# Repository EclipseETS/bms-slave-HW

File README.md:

# bms-slave-HW
Kicad project for slave board of the Eclipse solar car BMS

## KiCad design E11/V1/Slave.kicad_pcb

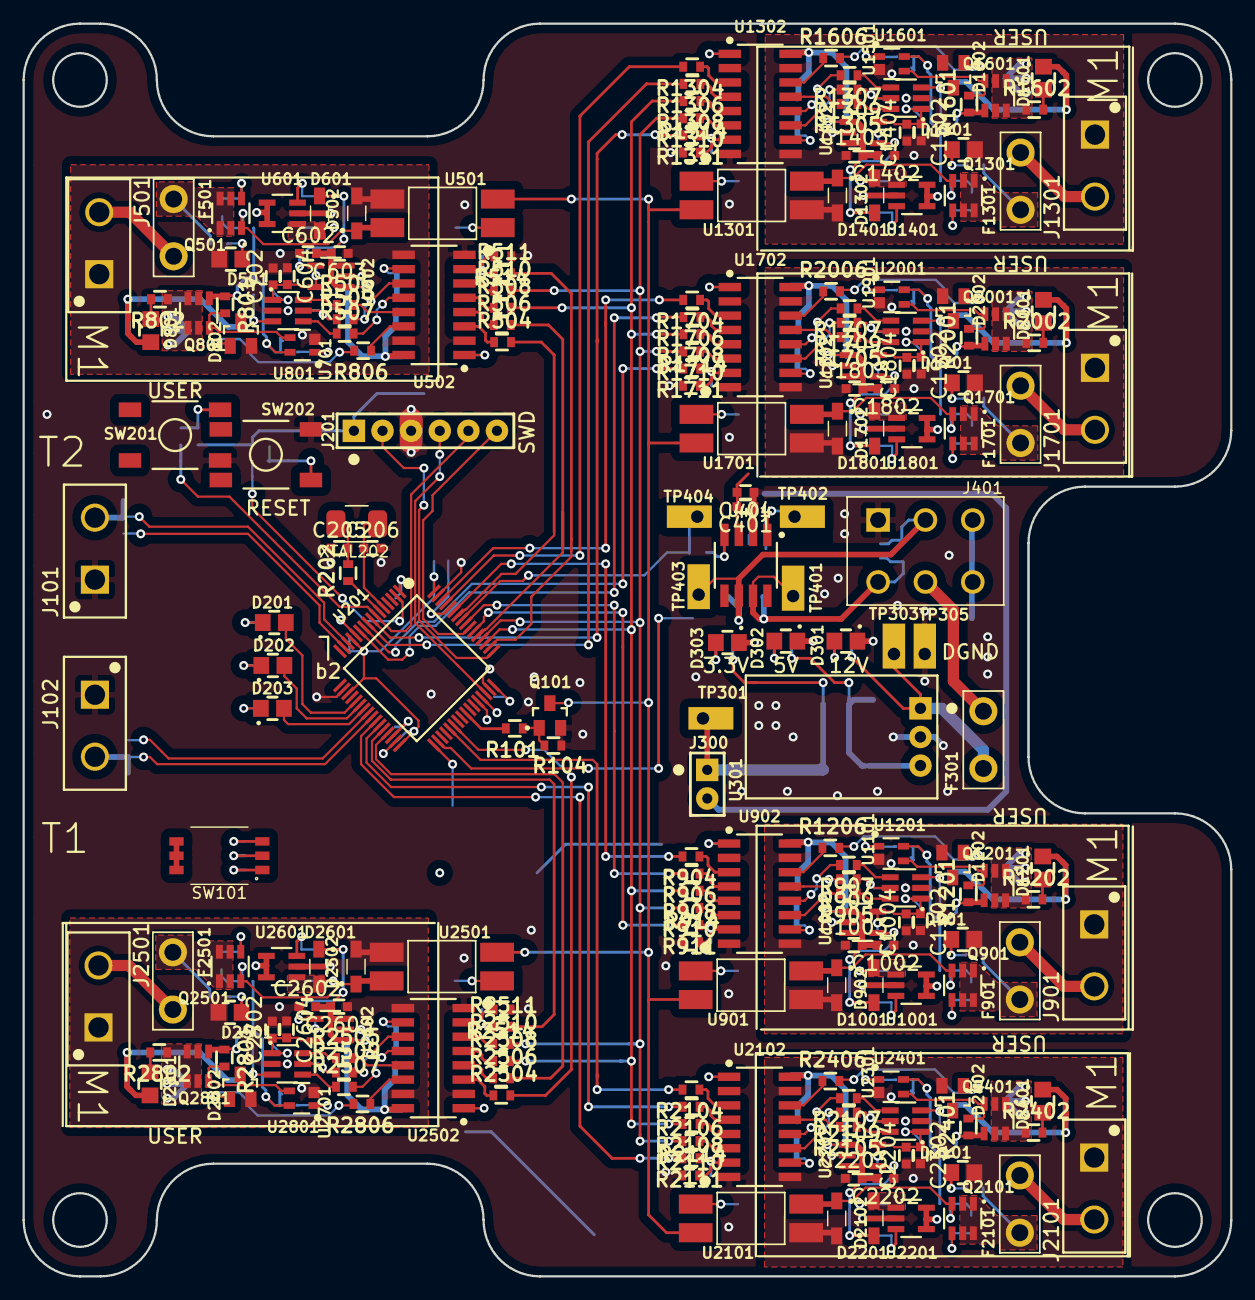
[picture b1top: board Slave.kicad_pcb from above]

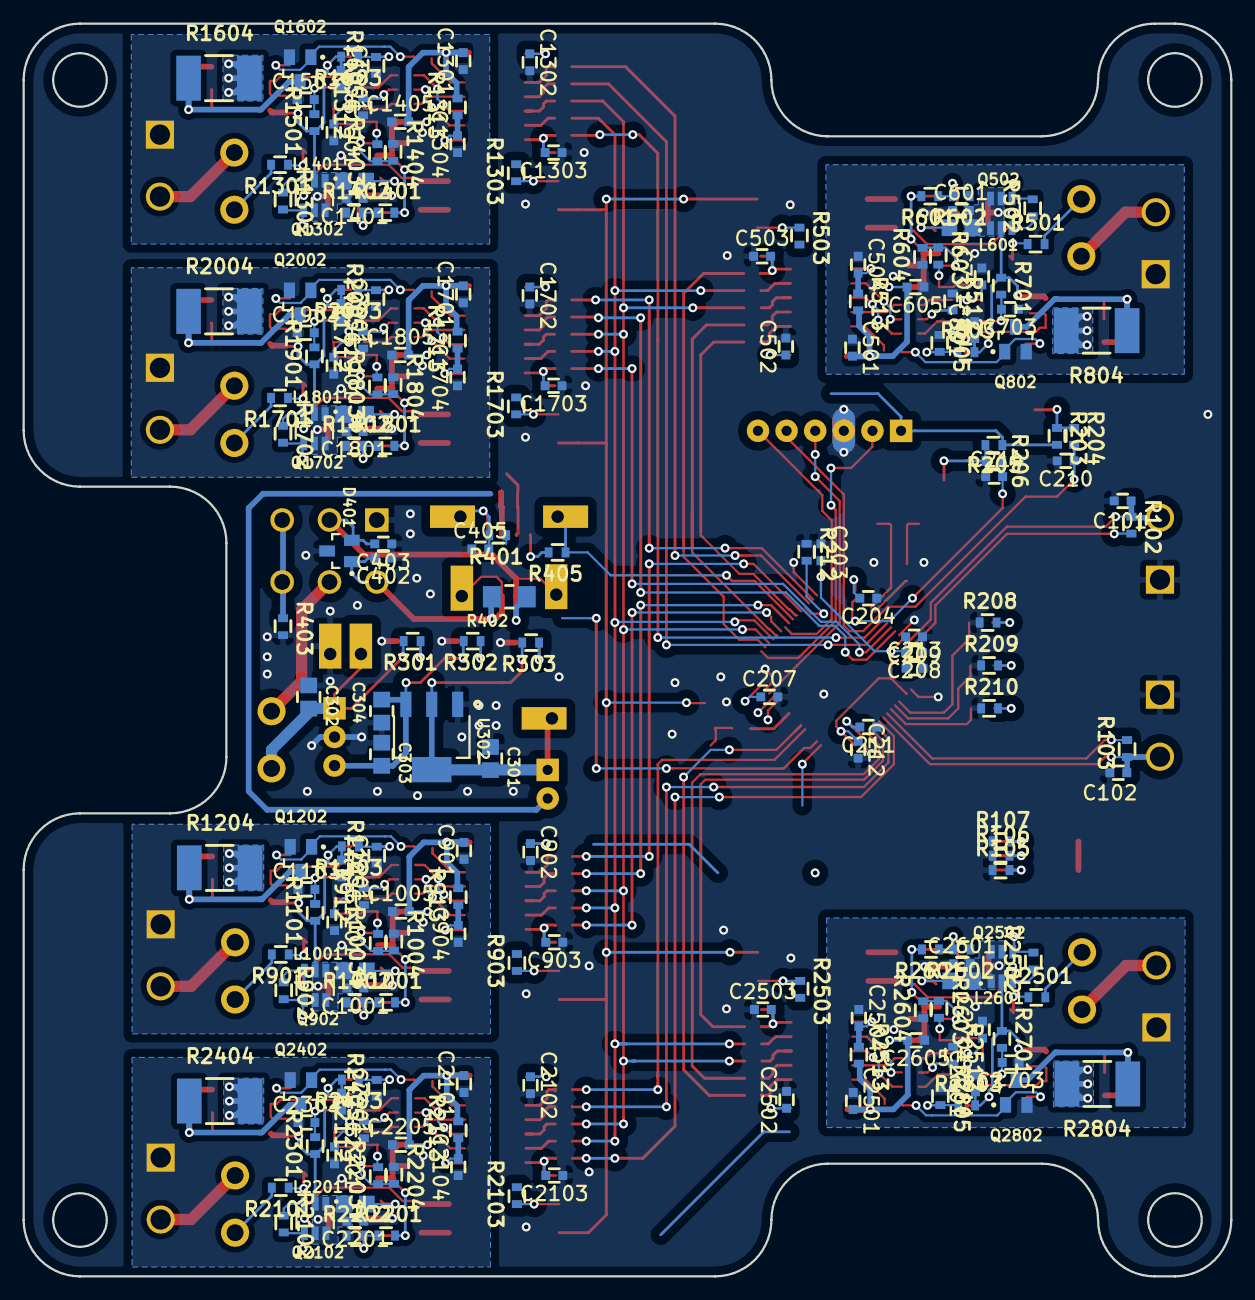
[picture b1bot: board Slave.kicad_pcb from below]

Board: 2 copper layers, 107.2 x 111.2 mm, 411 parts (191 on the bottom side), 263 nets.

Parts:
C101, C102, C204, C208, C401: 885012107015; C0603
C203, C207, C210, C212, C213, C214, C404: 885012207098; C0603
C205, C206, C402, C403: 885012007053; C0603
C209: 885012207092; C0603
C211: 885012107018; C0603
C301: 885012107005; C0805
C302, C303: 885012107018; C0805
C304: 885012107014; C0805
C405: 885012207080; C0603
C501, C502, C504, C702, C801, C901, C902, C904, C1102, C1201, C1301, C1302, C1304, C1502, C1601, C1701, C1702, C1704, C1902, C2001, C2101, C2102, C2104, C2302, C2401, C2501, C2502, C2504, C2702, C2801: 885012206095; C0603
C503, C903, C1303, C1703, C2103, C2503: 885012206077; C0603
C601, C602, C603, C604, C605, C1001, C1002, C1003, C1004, C1005, C1401, C1402, C1403, C1404, C1405, C1801, C1802, C1803, C1804, C1805, C2201, C2202, C2203, C2204, C2205, C2601, C2602, C2603, C2604, C2605: GRM188R61C106KAALD; C0603
C701, C1101, C1501, C1901, C2301, C2701: 885012106022; C0603
C703, C1103, C1503, C1903, C2303, C2703: 885012206073; C0603
D201, D301, D302, D303, D801, D1201, D1601, D2001, D2401, D2801: 150080VS75000; LED_0805_GREEN
D202: 150080YS75000; LED_0805_YELLOW
D203, D501, D901, D1301, D1701, D2101, D2501: 150080RS75000; LED_0805_RED
D401: D1213A-02SOL-7; SOT-23-3
D502, D601, D902, D1001, D1302, D1401, D1702, D1801, D2102, D2201, D2502, D2601: NSR0530HT1G; SOD-323
D802, D1202, D1602, D2002, D2402, D2802: MMBZ12VALT1G; SOT-23-3
F301, F501, F901, F1301, F1701, F2101, F2501: 39511000440; TE5_395
J101, J102, J501, J901, J1301, J1701, J2101, J2501: 64900221122
J201: Header_Male_Pin_2.54mm_1X6_,_Unshrouded; Headers_2.54mm_1X6
J300: Header_Male_Pin_2.54mm_1X2_,_Unshrouded; Headers_2.54mm_1X2
J401: 64900621122
L601, L1001, L1401, L1801, L2201, L2601: MLZ2012N101LT000; I0805
Q101: 2N7002P,215; SOT-23-3
Q501, Q502, Q801, Q901, Q902, Q1201, Q1301, Q1302, Q1601, Q1701, Q1702, Q2001, Q2101, Q2102, Q2401, Q2501, Q2502, Q2801: CPH6347-TL-W; TSOT-23-6
Q802, Q1202, Q1602, Q2002, Q2402, Q2802: BSS806NH6327XTSA1; SOT-23-3
R101, R208, R209, R210, R303: RC0805JR-07470RL; R0603
R102, R103: RC0805JR-0733KL; R0603
R104, R203, R205, R301: RC0805JR-074K7L; R0603
R105, R106, R107: RC0603JR-07470RL; R0603
R202, R403: RC0805JR-070RL; R0603
R204, R206, R401, R405: RC0805JR-07100RL; R0603
R212: RC0805JR-0710KL; R0603
R302: RC0805JR-071KL; R0603
R402: RC1206JR-07120RL; R1206
R501, R802, R901, R1202, R1301, R1602, R1701, R2002, R2101, R2402, R2501, R2802: RC0603JR-071KL; R0603
R502, R514, R801, R902, R914, R1201, R1302, R1314, R1601, R1702, R1714, R2001, R2102, R2114, R2401, R2502, R2514, R2801: RC0603JR-07470KL; R0603
R503, R903, R1303, R1703, R2103, R2503: RC0603JR-07330RL; R0603
R504, R505, R506, R507, R508, R509, R701, R904, R905, R906, R907, R908, R909, R1101, R1304, R1305, R1306, R1307, R1308, R1309, R1501, R1704, R1705, R1706, R1707, R1708, R1709, R1901, R2104, R2105, R2106, R2107, R2108, R2109, R2301, R2504, R2505, R2506, R2507, R2508, R2509, R2701: RC0603FR-07100RL; R0603
R510, R511, R512, R513, R603, R910, R911, R912, R913, R1003, R1310, R1311, R1312, R1313, R1403, R1710, R1711, R1712, R1713, R1803, R2110, R2111, R2112, R2113, R2203, R2510, R2511, R2512, R2513, R2603: RC0603JR-074K7L; R0603
R601, R1001, R1401, R1801, R2201, R2601: RC0603JR-071ML; R0603
R602, R1002, R1402, R1802, R2202, R2602: RC0603FR-07324KL; R0603
R604, R1004, R1404, R1804, R2204, R2604: RC0603FR-0712K1L; R0603
R803, R1203, R1603, R2003, R2403, R2803: RC0603JR-07560KL; R0603
R804, R1204, R1604, R2004, R2404, R2804: 352210RJT; R2512
R805, R1205, R1605, R2005, R2405, R2805: RC0603JR-07100KL; R0603
R806, R1206, R1606, R2006, R2406, R2806: RC0603JR-076K8L; R0603
SW101: DIP_SW_3; 416131160803
SW201, SW202: PTS645SM43SMTR92; PTS645_6X6X4_SMD
TP301, TP303, TP305, TP401, TP402, TP403, TP404: Test_Point_THM; Keystone_5001
U201: STM32F446RE; LQFP-64
U301: OKI-78SR-5/1.5-W36-C; OKI-78SR_Horizontal
U302: AZ1117IH-3.3TRG1; SOT-223-3
U401: SN65HVD232DR; SOIC-8
U501, U901, U1301, U1701, U2101, U2501: LTV-816S; 4-SMD
U502, U902, U1302, U1702, U2102, U2502: SI8641AB-B-IS1; SOIC-16
U601, U1001, U1401, U1801, U2201, U2601: AP3015KTR-G1; SOT-23-5
U602, U1002, U1402, U1802, U2202, U2602: AP2202K-ADJTRG1; SOT-23-5
U701, U1101, U1501, U1901, U2301, U2701: ADC121S021CIMF/NOPB; SOT-23-6
U801, U1201, U1601, U2001, U2401, U2801: ADCMP350YKSZ-REEL7; SC70-4
XTAL202: 7A-8.000MAHJ-T; TXC_7A_Series

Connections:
3.3V: C301.2, J300.1, R303.2, TP301.1, U302.2, U302.4
5V: C303.2, C304.2, R302.2, U301.3, U302.3
12V: C302.2, F301.2, R301.2, TP303.1, U301.1
/BALANCING_PWM_1: R504.2, U201.58
/BALANCING_PWM_2: R904.2, U201.59
/BALANCING_PWM_3: R1304.2, U201.61
/BALANCING_PWM_4: R1704.2, U201.62
/BALANCING_PWM_5: R2104.2, U201.37
/BALANCING_PWM_6: R2504.2, U201.38
/CAN1/CAN_N: C403.2, D401.2, J401.2, R402.2, TP403.1, U401.6
/CAN1/CAN_P: C402.2, D401.1, J401.4, R402.1, TP401.1, U401.7
/CAN1/Shield1: J401.3, J401.6, R403.1
/CAN2_RX: R405.1, TP404.1, U201.57
/CAN2_TX: R401.1, U201.34
/CS_1: R506.2, U201.53
/CS_2: R906.2, U201.56
/CS_3: R1306.2, U201.9
/CS_4: R1706.2, U201.11
/CS_5: R2106.2, U201.27
/CS_6: R2506.2, U201.29
/DATA_ENABLE_1: R511.2, U201.50
/DATA_ENABLE_2: R911.2, U201.54
/DATA_ENABLE_3: R1311.2, U201.8
/DATA_ENABLE_4: R1711.2, U201.10
/DATA_ENABLE_5: R2111.2, U201.26
/DATA_ENABLE_6: R2511.2, U201.28
/ID_0: R105.2, SW101.1, U201.33
/ID_1: R106.2, SW101.2, U201.44
/ID_2: R107.2, SW101.3, U201.45
/MISO: R510.2, R910.2, R1310.2, R1710.2, R2110.2, R2510.2, U201.52
/Module 1/+VREF: C604.2, C701.1, C702.1, R603.2, U602.5, U701.1
/Module 1/BALANCE_PWM: R806.1, U502.14
/Module 1/BVDD: C501.2, C602.2, C603.2, C605.2, D601.1, R513.2, R601.2, U502.16, U602.1, U602.3
/Module 1/Balancing/Drain_P_Mosfet: Q801.1, Q801.2, Q801.5, Q801.6, R802.1, R804.2
/Module 1/CELL+: F501.2, Q501.1, Q501.2, Q501.5, Q501.6, R501.2
/Module 1/CELL-: C501.1, C504.1, C601.1, C602.1, C603.1, C604.1, C605.1, C701.2, C702.2, C703.1, C801.2, D501.2, D502.2, D802.2, J501.1, Q802.2, R512.1, R602.1, R604.1, R805.1, U501.3, U502.9, U502.15, U601.2, U602.2, U701.2, U801.2
/Module 1/CELL_Voltage: C601.2, C801.1, L601.1, Q502.1, Q502.2, Q502.5, Q502.6, Q801.4, R701.1, R801.1, R803.2, U601.4, U601.5, U801.4
/Module 1/CS: R505.2, U502.13
/Module 1/Power Supply Front End/SW: D601.2, L601.2, U601.1
/Module 1/SCLK: R507.2, U502.12
/Module 1/SDATA: R509.2, U502.11
/Module 1/Voltage Reading/CS: R505.1, U701.6
/Module 1/Voltage Reading/SCLK: R507.1, U701.4
/Module 1/Voltage Reading/SDATA: R509.1, R512.2, U701.5
/Module 2/+VREF: C1004.2, C1101.1, C1102.1, R1003.2, U1002.5, U1101.1
/Module 2/BALANCE_PWM: R1206.1, U902.14
/Module 2/BVDD: C901.2, C1002.2, C1003.2, C1005.2, D1001.1, R913.2, R1001.2, U902.16, U1002.1, U1002.3
/Module 2/Balancing/Drain_P_Mosfet: Q1201.1, Q1201.2, Q1201.5, Q1201.6, R1202.1, R1204.2
/Module 2/CELL+: F901.2, Q901.1, Q901.2, Q901.5, Q901.6, R901.2
/Module 2/CELL-: C901.1, C904.1, C1001.1, C1002.1, C1003.1, C1004.1, C1005.1, C1101.2, C1102.2, C1103.1, C1201.2, D901.2, D902.2, D1202.2, J901.1, Q1202.2, R912.1, R1002.1, R1004.1, R1205.1, U901.3, U902.9, U902.15, U1001.2, U1002.2, U1101.2, U1201.2
/Module 2/CELL_Voltage: C1001.2, C1201.1, L1001.1, Q902.1, Q902.2, Q902.5, Q902.6, Q1201.4, R1101.1, R1201.1, R1203.2, U1001.4, U1001.5, U1201.4
/Module 2/CS: R905.2, U902.13
/Module 2/Power Supply Front End/SW: D1001.2, L1001.2, U1001.1
/Module 2/SCLK: R907.2, U902.12
/Module 2/SDATA: R909.2, U902.11
/Module 2/Voltage Reading/CS: R905.1, U1101.6
/Module 2/Voltage Reading/SCLK: R907.1, U1101.4
/Module 2/Voltage Reading/SDATA: R909.1, R912.2, U1101.5
/Module 3/+VREF: C1404.2, C1501.1, C1502.1, R1403.2, U1402.5, U1501.1
/Module 3/BALANCE_PWM: R1606.1, U1302.14
/Module 3/BVDD: C1301.2, C1402.2, C1403.2, C1405.2, D1401.1, R1313.2, R1401.2, U1302.16, U1402.1, U1402.3
/Module 3/Balancing/Drain_P_Mosfet: Q1601.1, Q1601.2, Q1601.5, Q1601.6, R1602.1, R1604.2
/Module 3/CELL+: F1301.2, Q1301.1, Q1301.2, Q1301.5, Q1301.6, R1301.2
/Module 3/CELL-: C1301.1, C1304.1, C1401.1, C1402.1, C1403.1, C1404.1, C1405.1, C1501.2, C1502.2, C1503.1, C1601.2, D1301.2, D1302.2, D1602.2, J1301.1, Q1602.2, R1312.1, R1402.1, R1404.1, R1605.1, U1301.3, U1302.9, U1302.15, U1401.2, U1402.2, U1501.2, U1601.2
/Module 3/CELL_Voltage: C1401.2, C1601.1, L1401.1, Q1302.1, Q1302.2, Q1302.5, Q1302.6, Q1601.4, R1501.1, R1601.1, R1603.2, U1401.4, U1401.5, U1601.4
/Module 3/CS: R1305.2, U1302.13
/Module 3/Power Supply Front End/SW: D1401.2, L1401.2, U1401.1
/Module 3/SCLK: R1307.2, U1302.12
/Module 3/SDATA: R1309.2, U1302.11
/Module 3/Voltage Reading/CS: R1305.1, U1501.6
/Module 3/Voltage Reading/SCLK: R1307.1, U1501.4
/Module 3/Voltage Reading/SDATA: R1309.1, R1312.2, U1501.5
/Module 4/+VREF: C1804.2, C1901.1, C1902.1, R1803.2, U1802.5, U1901.1
/Module 4/BALANCE_PWM: R2006.1, U1702.14
/Module 4/BVDD: C1701.2, C1802.2, C1803.2, C1805.2, D1801.1, R1713.2, R1801.2, U1702.16, U1802.1, U1802.3
/Module 4/Balancing/Drain_P_Mosfet: Q2001.1, Q2001.2, Q2001.5, Q2001.6, R2002.1, R2004.2
/Module 4/CELL+: F1701.2, Q1701.1, Q1701.2, Q1701.5, Q1701.6, R1701.2
/Module 4/CELL-: C1701.1, C1704.1, C1801.1, C1802.1, C1803.1, C1804.1, C1805.1, C1901.2, C1902.2, C1903.1, C2001.2, D1701.2, D1702.2, D2002.2, J1701.1, Q2002.2, R1712.1, R1802.1, R1804.1, R2005.1, U1701.3, U1702.9, U1702.15, U1801.2, U1802.2, U1901.2, U2001.2
/Module 4/CELL_Voltage: C1801.2, C2001.1, L1801.1, Q1702.1, Q1702.2, Q1702.5, Q1702.6, Q2001.4, R1901.1, R2001.1, R2003.2, U1801.4, U1801.5, U2001.4
/Module 4/CS: R1705.2, U1702.13
/Module 4/Power Supply Front End/SW: D1801.2, L1801.2, U1801.1
/Module 4/SCLK: R1707.2, U1702.12
/Module 4/SDATA: R1709.2, U1702.11
/Module 4/Voltage Reading/CS: R1705.1, U1901.6
/Module 4/Voltage Reading/SCLK: R1707.1, U1901.4
/Module 4/Voltage Reading/SDATA: R1709.1, R1712.2, U1901.5
/Module 5/+VREF: C2204.2, C2301.1, C2302.1, R2203.2, U2202.5, U2301.1
/Module 5/BALANCE_PWM: R2406.1, U2102.14
/Module 5/BVDD: C2101.2, C2202.2, C2203.2, C2205.2, D2201.1, R2113.2, R2201.2, U2102.16, U2202.1, U2202.3
/Module 5/Balancing/Drain_P_Mosfet: Q2401.1, Q2401.2, Q2401.5, Q2401.6, R2402.1, R2404.2
/Module 5/CELL+: F2101.2, Q2101.1, Q2101.2, Q2101.5, Q2101.6, R2101.2
/Module 5/CELL-: C2101.1, C2104.1, C2201.1, C2202.1, C2203.1, C2204.1, C2205.1, C2301.2, C2302.2, C2303.1, C2401.2, D2101.2, D2102.2, D2402.2, J2101.1, Q2402.2, R2112.1, R2202.1, R2204.1, R2405.1, U2101.3, U2102.9, U2102.15, U2201.2, U2202.2, U2301.2, U2401.2
/Module 5/CELL_Voltage: C2201.2, C2401.1, L2201.1, Q2102.1, Q2102.2, Q2102.5, Q2102.6, Q2401.4, R2301.1, R2401.1, R2403.2, U2201.4, U2201.5, U2401.4
/Module 5/CS: R2105.2, U2102.13
/Module 5/Power Supply Front End/SW: D2201.2, L2201.2, U2201.1
/Module 5/SCLK: R2107.2, U2102.12
/Module 5/SDATA: R2109.2, U2102.11
/Module 5/Voltage Reading/CS: R2105.1, U2301.6
/Module 5/Voltage Reading/SCLK: R2107.1, U2301.4
/Module 5/Voltage Reading/SDATA: R2109.1, R2112.2, U2301.5
/Module 6/+VREF: C2604.2, C2701.1, C2702.1, R2603.2, U2602.5, U2701.1
/Module 6/BALANCE_PWM: R2806.1, U2502.14
/Module 6/BVDD: C2501.2, C2602.2, C2603.2, C2605.2, D2601.1, R2513.2, R2601.2, U2502.16, U2602.1, U2602.3
/Module 6/Balancing/Drain_P_Mosfet: Q2801.1, Q2801.2, Q2801.5, Q2801.6, R2802.1, R2804.2
/Module 6/CELL+: F2501.2, Q2501.1, Q2501.2, Q2501.5, Q2501.6, R2501.2
/Module 6/CELL-: C2501.1, C2504.1, C2601.1, C2602.1, C2603.1, C2604.1, C2605.1, C2701.2, C2702.2, C2703.1, C2801.2, D2501.2, D2502.2, D2802.2, J2501.1, Q2802.2, R2512.1, R2602.1, R2604.1, R2805.1, U2501.3, U2502.9, U2502.15, U2601.2, U2602.2, U2701.2, U2801.2
/Module 6/CELL_Voltage: C2601.2, C2801.1, L2601.1, Q2502.1, Q2502.2, Q2502.5, Q2502.6, Q2801.4, R2701.1, R2801.1, R2803.2, U2601.4, U2601.5, U2801.4
/Module 6/CS: R2505.2, U2502.13
/Module 6/Power Supply Front End/SW: D2601.2, L2601.2, U2601.1
/Module 6/SCLK: R2507.2, U2502.12
/Module 6/SDATA: R2509.2, U2502.11
/Module 6/Voltage Reading/CS: R2505.1, U2701.6
/Module 6/Voltage Reading/SCLK: R2507.1, U2701.4
/Module 6/Voltage Reading/SDATA: R2509.1, R2512.2, U2701.5
/NRST: C210.1, J201.5, R204.2, U201.7
/NTC_1_ADC: C101.2, J101.2, R102.1, U201.14
/NTC_1_GPIO: R102.2, U201.15
/NTC_2_ADC: C102.2, J102.2, R103.1, U201.25
/NTC_2_GPIO: R103.2, U201.24
/PA5: D201.2, U201.21
/PA6: D202.2, U201.22
/PA7: D203.2, U201.23
/PWR_ENABLE: Q101.3, U501.2, U901.2, U1301.2, U1701.2, U2101.2, U2501.2
/PWR_ENABLE_GPIO: R101.2, U201.41
/SCLK: R508.2, R908.2, R1308.2, R1708.2, R2108.2, R2508.2, U201.51
/STM32F446/SWCLK: J201.2, U201.49
/STM32F446/SWDIO: J201.4, U201.46
/STM32F446/SWO: J201.6, U201.55
/STM32F446/USER_BTN: C214.1, R206.2, U201.2
/VBat: C204.2, U201.1
CAN_PWR: F301.1, J401.5
DGND: C101.1, C102.1, C203.1, C204.1, C205.1, C206.2, C207.2, C208.1, C209.1, C210.2, C211.1, C212.2, C213.2, C214.2, C301.1, C302.1, C303.1, C304.1, C401.1, C402.1, C403.1, C404.1, C405.1, C502.2, C503.1, C902.2, C903.1, C1302.2, C1303.1, C1702.2, C1703.1, C2102.2, C2103.1, C2502.2, C2503.1, D301.1, D302.1, D303.1, D401.3, J101.1, J102.1, J201.3, J401.1, Q101.2, R104.1, R105.1, R106.1, R107.1, R208.1, R209.1, R210.1, R212.1, R403.2, R514.1, R914.1, R1314.1, R1714.1, R2114.1, R2514.1, SW201.4, SW202.3, TP305.1, U201.12, U201.18, U201.31, U201.47, U201.63, U301.2, U302.1, U401.2, U502.2, U502.8, U902.2, U902.8, U1302.2, U1302.8, U1702.2, U1702.8, U2102.2, U2102.8, U2502.2, U2502.8
unnamed: C205.2, R202.2, XTAL202.1
unnamed: C206.1, U201.5, XTAL202.2
unnamed: C211.2, U201.30
unnamed: C405.2, R401.2, TP402.1, U401.1
unnamed: C503.2, R511.1, R514.2, U502.7
unnamed: C504.2, R513.1, U502.10
unnamed: C703.2, R701.2, U701.3
unnamed: C903.2, R911.1, R914.2, U902.7
unnamed: C904.2, R913.1, U902.10
unnamed: C1103.2, R1101.2, U1101.3
unnamed: C1303.2, R1311.1, R1314.2, U1302.7
unnamed: C1304.2, R1313.1, U1302.10
unnamed: C1503.2, R1501.2, U1501.3
unnamed: C1703.2, R1711.1, R1714.2, U1702.7
unnamed: C1704.2, R1713.1, U1702.10
unnamed: C1903.2, R1901.2, U1901.3
unnamed: C2103.2, R2111.1, R2114.2, U2102.7
unnamed: C2104.2, R2113.1, U2102.10
unnamed: C2303.2, R2301.2, U2301.3
unnamed: C2503.2, R2511.1, R2514.2, U2502.7
unnamed: C2504.2, R2513.1, U2502.10
unnamed: C2703.2, R2701.2, U2701.3
unnamed: D201.1, R208.2
unnamed: D202.1, R209.2
unnamed: D203.1, R210.2
unnamed: D301.2, R301.1
unnamed: D302.2, R302.1
unnamed: D303.2, R303.1
unnamed: D501.1, R501.1
unnamed: D502.1, Q501.3, Q502.3, R502.1, U501.4
unnamed: D801.1, Q802.3, R804.1
unnamed: D801.2, R802.2
unnamed: D802.1, Q802.1, R806.2
unnamed: D901.1, R901.1
unnamed: D902.1, Q901.3, Q902.3, R902.1, U901.4
unnamed: D1201.1, Q1202.3, R1204.1
unnamed: D1201.2, R1202.2
unnamed: D1202.1, Q1202.1, R1206.2
unnamed: D1301.1, R1301.1
unnamed: D1302.1, Q1301.3, Q1302.3, R1302.1, U1301.4
unnamed: D1601.1, Q1602.3, R1604.1
unnamed: D1601.2, R1602.2
unnamed: D1602.1, Q1602.1, R1606.2
unnamed: D1701.1, R1701.1
unnamed: D1702.1, Q1701.3, Q1702.3, R1702.1, U1701.4
unnamed: D2001.1, Q2002.3, R2004.1
unnamed: D2001.2, R2002.2
unnamed: D2002.1, Q2002.1, R2006.2
unnamed: D2101.1, R2101.1
unnamed: D2102.1, Q2101.3, Q2102.3, R2102.1, U2101.4
unnamed: D2401.1, Q2402.3, R2404.1
unnamed: D2401.2, R2402.2
unnamed: D2402.1, Q2402.1, R2406.2
unnamed: D2501.1, R2501.1
unnamed: D2502.1, Q2501.3, Q2502.3, R2502.1, U2501.4
unnamed: D2801.1, Q2802.3, R2804.1
unnamed: D2801.2, R2802.2
unnamed: D2802.1, Q2802.1, R2806.2
unnamed: F501.1, J501.2
unnamed: F901.1, J901.2
unnamed: F1301.1, J1301.2
unnamed: F1701.1, J1701.2
unnamed: F2101.1, J2101.2
unnamed: F2501.1, J2501.2
unnamed: Q101.1, R101.1, R104.2
unnamed: Q501.4, Q502.4, R502.2
unnamed: Q801.3, R801.2, U801.3
unnamed: Q901.4, Q902.4, R902.2
unnamed: Q1201.3, R1201.2, U1201.3
unnamed: Q1301.4, Q1302.4, R1302.2
unnamed: Q1601.3, R1601.2, U1601.3
unnamed: Q1701.4, Q1702.4, R1702.2
unnamed: Q2001.3, R2001.2, U2001.3
unnamed: Q2101.4, Q2102.4, R2102.2
unnamed: Q2401.3, R2401.2, U2401.3
unnamed: Q2501.4, Q2502.4, R2502.2
unnamed: Q2801.3, R2801.2, U2801.3
unnamed: R202.1, U201.6
unnamed: R203.1, R204.1, SW201.2
unnamed: R205.1, R206.1, SW202.1
unnamed: R212.2, U201.60
unnamed: R405.2, U401.4
unnamed: R503.1, U501.1
unnamed: R504.1, U502.3
unnamed: R506.1, U502.4
unnamed: R508.1, U502.5
unnamed: R510.1, U502.6
unnamed: R601.1, R602.2, U601.3
unnamed: R603.1, R604.2, U602.4
unnamed: R803.1, R805.2, U801.1
unnamed: R903.1, U901.1
unnamed: R904.1, U902.3
unnamed: R906.1, U902.4
unnamed: R908.1, U902.5
unnamed: R910.1, U902.6
unnamed: R1001.1, R1002.2, U1001.3
unnamed: R1003.1, R1004.2, U1002.4
unnamed: R1203.1, R1205.2, U1201.1
unnamed: R1303.1, U1301.1
unnamed: R1304.1, U1302.3
unnamed: R1306.1, U1302.4
unnamed: R1308.1, U1302.5
unnamed: R1310.1, U1302.6
unnamed: R1401.1, R1402.2, U1401.3
unnamed: R1403.1, R1404.2, U1402.4
unnamed: R1603.1, R1605.2, U1601.1
unnamed: R1703.1, U1701.1
unnamed: R1704.1, U1702.3
unnamed: R1706.1, U1702.4
unnamed: R1708.1, U1702.5
unnamed: R1710.1, U1702.6
unnamed: R1801.1, R1802.2, U1801.3
unnamed: R1803.1, R1804.2, U1802.4
unnamed: R2003.1, R2005.2, U2001.1
unnamed: R2103.1, U2101.1
unnamed: R2104.1, U2102.3
unnamed: R2106.1, U2102.4
unnamed: R2108.1, U2102.5
unnamed: R2110.1, U2102.6
unnamed: R2201.1, R2202.2, U2201.3
unnamed: R2203.1, R2204.2, U2202.4
unnamed: R2403.1, R2405.2, U2401.1
unnamed: R2503.1, U2501.1
unnamed: R2504.1, U2502.3
unnamed: R2506.1, U2502.4
unnamed: R2508.1, U2502.5
unnamed: R2510.1, U2502.6
unnamed: R2601.1, R2602.2, U2601.3
unnamed: R2603.1, R2604.2, U2602.4
unnamed: R2803.1, R2805.2, U2801.1
VDD: C203.2, C207.1, C208.2, C209.2, C212.1, C213.1, C401.2, C404.2, C502.1, C902.1, C1302.1, C1702.1, C2102.1, C2502.1, J201.1, J300.2, R203.2, R205.2, R503.2, R903.2, R1303.2, R1703.2, R2103.2, R2503.2, SW101.4, SW101.5, SW101.6, U201.13, U201.19, U201.32, U201.48, U201.64, U401.3, U502.1, U902.1, U1302.1, U1702.1, U2102.1, U2502.1

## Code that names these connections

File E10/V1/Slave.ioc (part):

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Mcu.Name=STM32F446R(C-E)Tx
Mcu.Package=LQFP64
Mcu.UserName=STM32F446RETx
PA0-WKUP.GPIOParameters=GPIO_Label
PA0-WKUP.GPIO_Label=NTC_1_ADC
PA0-WKUP.Signal=ADCx_IN0
PA1.GPIOParameters=GPIO_Label
PA1.GPIO_Label=NTC_1_EN
PA1.Signal=GPIO_Output
PA10.GPIOParameters=GPIO_Label
PA10.GPIO_Label=CS_8
PA10.Signal=GPIO_Output
PA11.GPIOParameters=GPIO_Label
PA11.GPIO_Label=ID_1
PA11.Signal=GPIO_Output
PA12.GPIOParameters=GPIO_Label
PA12.GPIO_Label=ID_2
PA12.Signal=GPIO_Output
PA13.GPIOParameters=GPIO_Label
PA13.GPIO_Label=TMS
PA13.Signal=SYS_JTMS-SWDIO
PA14.GPIOParameters=GPIO_Label
PA14.GPIO_Label=TCK
PA14.Signal=SYS_JTCK-SWCLK
PA15.GPIOParameters=GPIO_Label
PA15.GPIO_Label=DE_1
PA15.Signal=GPIO_Output
PA2.GPIOParameters=GPIO_Label
PA2.GPIO_Label=USART_TX
PA2.Mode=Asynchronous
PA2.Signal=USART2_TX
PA3.GPIOParameters=GPIO_Label
PA3.GPIO_Label=USART_RX
PA3.Mode=Asynchronous
PA3.Signal=USART2_RX
PA5.GPIOParameters=GPIO_Label
PA5.GPIO_Label=LED_BLINK
PA5.Signal=GPIO_Output
PA6.GPIOParameters=GPIO_Label
PA6.GPIO_Label=LED_DEBUG
PA6.Signal=GPIO_Output
PA7.GPIOParameters=GPIO_Label
PA7.GPIO_Label=LED_ERROR
PA7.Signal=GPIO_Output
PA8.GPIOParameters=GPIO_Label
PA8.GPIO_Label=POWER_EN
PA8.Signal=GPIO_Output
PA9.GPIOParameters=GPIO_Label
PA9.GPIO_Label=DE_8
PA9.Signal=GPIO_Output
PB0.GPIOParameters=GPIO_Label
PB0.GPIO_Label=DE_5
PB0.Signal=GPIO_Output
PB1.GPIOParameters=GPIO_Label
PB1.GPIO_Label=CS_5
PB1.Signal=GPIO_Output
PB10.GPIOParameters=GPIO_Label
PB10.GPIO_Label=CS_6
PB10.Signal=GPIO_Output
PB12.GPIOParameters=GPIO_Label
PB12.GPIO_Label=ID_0
PB12.Signal=GPIO_Output
PB13.Mode=Slave
PB13.Signal=CAN2_TX
PB14.GPIOParameters=GPIO_Label
PB14.GPIO_Label=DE_7
PB14.Signal=GPIO_Output
PB15.GPIOParameters=GPIO_Label
PB15.GPIO_Label=CS_7
PB15.Signal=GPIO_Output
PB2.GPIOParameters=GPIO_Label
PB2.GPIO_Label=DE_6
PB2.Signal=GPIO_Output
PB3.GPIOParameters=GPIO_Label
PB3.GPIO_Label=SWO
PB3.Signal=SYS_JTDO-SWO
PB4.GPIOParameters=GPIO_Label
PB4.GPIO_Label=CS_2
PB4.Signal=GPIO_Output
PB5.Mode=Slave
PB5.Signal=CAN2_RX
PB6.GPIOParameters=GPIO_Label
PB6.GPIO_Label=BALANCING_PWM_5
PB6.Signal=S_TIM4_CH1
PB7.GPIOParameters=GPIO_Label
PB7.GPIO_Label=BALANCING_PWM_6
PB7.Signal=S_TIM4_CH2
PB8.GPIOParameters=GPIO_Label
PB8.GPIO_Label=BALANCING_PWM_7
PB8.Signal=S_TIM4_CH3
PB9.GPIOParameters=GPIO_Label
PB9.GPIO_Label=BALANCING_PWM_8
PB9.Signal=S_TIM4_CH4
PC0.GPIOParameters=GPIO_Label
PC0.GPIO_Label=DE_3
PC0.Signal=GPIO_Output
PC1.GPIOParameters=GPIO_Label
PC1.GPIO_Label=CS_3
PC1.Signal=GPIO_Output
PC10.Mode=RX_Only_Simplex_Unidirect_Master
PC10.Signal=SPI3_SCK
PC11.Mode=RX_Only_Simplex_Unidirect_Master
PC11.Signal=SPI3_MISO
PC12.GPIOParameters=GPIO_Label
PC12.GPIO_Label=CS_1
PC12.Signal=GPIO_Output
PC13.GPIOParameters=GPIO_Label,GPIO_ModeDefaultEXTI
PC13.GPIO_Label=BTN_USER
PC13.GPIO_ModeDefaultEXTI=GPIO_MODE_EVT_RISING
PC13.Signal=GPXTI13
PC14-OSC32_IN.Signal=RCC_OSC32_IN
PC15-OSC32_OUT.Signal=RCC_OSC32_OUT
PC2.GPIOParameters=GPIO_Label
PC2.GPIO_Label=DE_4
PC2.Signal=GPIO_Output
PC3.GPIOParameters=GPIO_Label
PC3.GPIO_Label=CS_4
PC3.Signal=GPIO_Output
PC4.GPIOParameters=GPIO_Label
PC4.GPIO_Label=NTC_2_EN
PC4.Signal=GPIO_Output
PC5.GPIOParameters=GPIO_Label
PC5.GPIO_Label=NTC_2_ADC
PC5.Signal=ADCx_IN15
PC6.GPIOParameters=GPIO_Label
PC6.GPIO_Label=BALANCING_PWM_1
PC6.Signal=S_TIM8_CH1
PC7.GPIOParameters=GPIO_Label
PC7.GPIO_Label=BALANCING_PWM_2
PC7.Signal=S_TIM8_CH2
PC8.GPIOParameters=GPIO_Label
PC8.GPIO_Label=BALANCING_PWM_3
PC8.Signal=S_TIM8_CH3
PC9.GPIOParameters=GPIO_Label
PC9.GPIO_Label=BALANCING_PWM_4
PC9.Signal=S_TIM8_CH4
PD2.GPIOParameters=GPIO_Label
PD2.GPIO_Label=DE_2
PD2.Signal=GPIO_Output
PH0-OSC_IN.Mode=HSE-External-Oscillator
PH0-OSC_IN.Signal=RCC_OSC_IN
PH1-OSC_OUT.Mode=HSE-External-Oscillator
PH1-OSC_OUT.Signal=RCC_OSC_OUT
RCC.HSE_VALUE=8000000
RCC.SYSCLKFreq_VALUE=180000000
RCC.SYSCLKSource=RCC_SYSCLKSOURCE_PLLCLK
board=NUCLEO-F446RE
boardIOC=true

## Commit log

2020-05-03 Add gitignore
2020-05-03 Add E10 Slave and create E11 folder for new design
2020-05-04 start of project on new branch
2020-05-04 update for missing resistor
2020-06-12 begin mod module 0805 to 0603 res and caps
2020-06-13 size reduction of modules using 0603 components
2020-06-26 progress save
2020-09-07 most of the parts have been migrated to new board outline
2020-09-09 initial component placement done
2020-09-17 updated filter values and pcb
2020-10-06 routing
2020-12-22 save
2021-01-02 more routing
2021-01-23 optimization time
